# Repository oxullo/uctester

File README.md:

# uctester

Ultimate Continuity tester or Leo's ideal tool for continuity testing.

The design of the tool is described here: https://www.youtube.com/watch?v=N2M-p-OGvPg

A description of an implementation of such design can be found here: https://www.xul.it/blog/index.php/2020/08/15/the-ultimate-continuity-tester/

## Eagle

This repo stores the production files of the tool, with sources for Eagle and a Gerber export. All the files are released under the MIT license, with the permission of the original author.

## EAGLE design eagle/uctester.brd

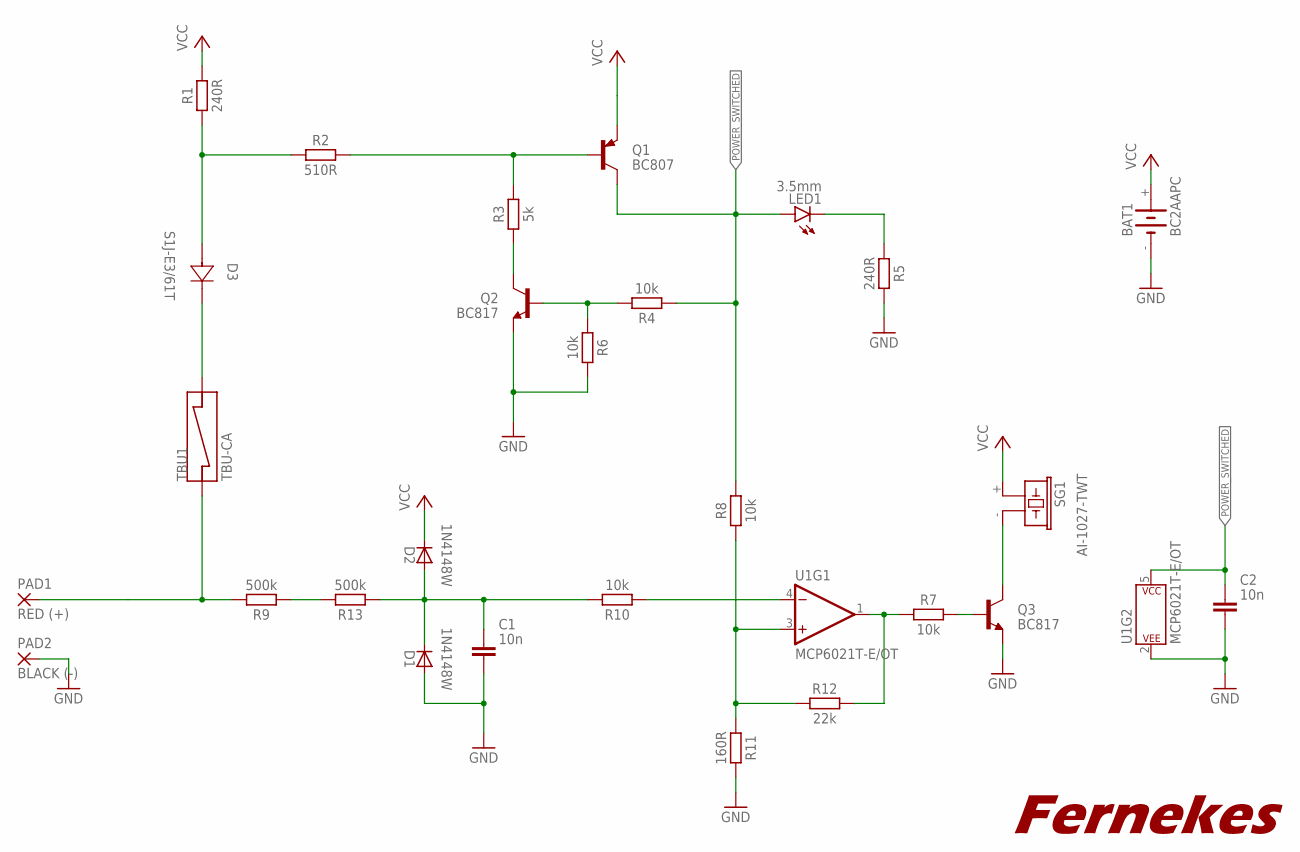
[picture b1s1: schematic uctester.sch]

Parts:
BAT1: BC2AAPC
C1, C2: 10n; CAPC3216X135
D1, D2: 1N4148W; SOD-123
D3: S1J-E3/61T; DIODE_DO214AC
LED1: 3.5mm; LED5MM
PAD1: RED (+); SMD2,54-5,08
PAD2: BLACK (-); SMD2,54-5,08
Q1: BC807; SOT23-BEC
Q2, Q3: BC817; SOT23-BEC
R1, R5: 240R; RESC3216X70
R2: 510R; RESC3216X70
R3: 5k; RESC3216X70
R4, R6, R7, R8, R10: 10k; RESC3216X70
R9, R13: 500k; RESC3216X70
R11: 160R; RESC3216X70
R12: 22k; RESC3216X70
SG1: AI-1027-TWT
TBU1: TBU-CA; RESDFN650X400X90-2N
U1: MCP6021T-E/OT; SOT95P280X145-5N

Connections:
GND: BAT1.-, C1.2, C2.2, D1.A, PAD2.1, Q2.E, Q3.E, R5.2, R6.2, R11.2, U1.2 (P$V-)
unnamed: Q2.C, R3.1
unnamed: Q2.B, R4.2, R6.1
unnamed: R9.1, R13.2
unnamed: R10.1, U1.4 (-IN)
unnamed: R8.1, R11.1, R12.1, U1.3 (+IN)
unnamed: R7.1, R12.2, U1.1 (OUT)
unnamed: Q3.B, R7.2
unnamed: Q3.C, SG1.- (2)
unnamed: Q1.B, R2.2, R3.2
unnamed: C1.1, D1.C, D2.A, R10.2, R13.1
unnamed: D3.2 (A), R1.1, R2.1
unnamed: PAD1.1, R9.2, TBU1.1
unnamed: LED1.K (C), R5.1
unnamed: D3.1 (C), TBU1.3
POWER_SWITCHED: C2.1, LED1.A, Q1.C, R4.1, R8.2, U1.5 (P$V+)
VCC: BAT1.+, D2.C, Q1.E, R1.2, SG1.+ (1)

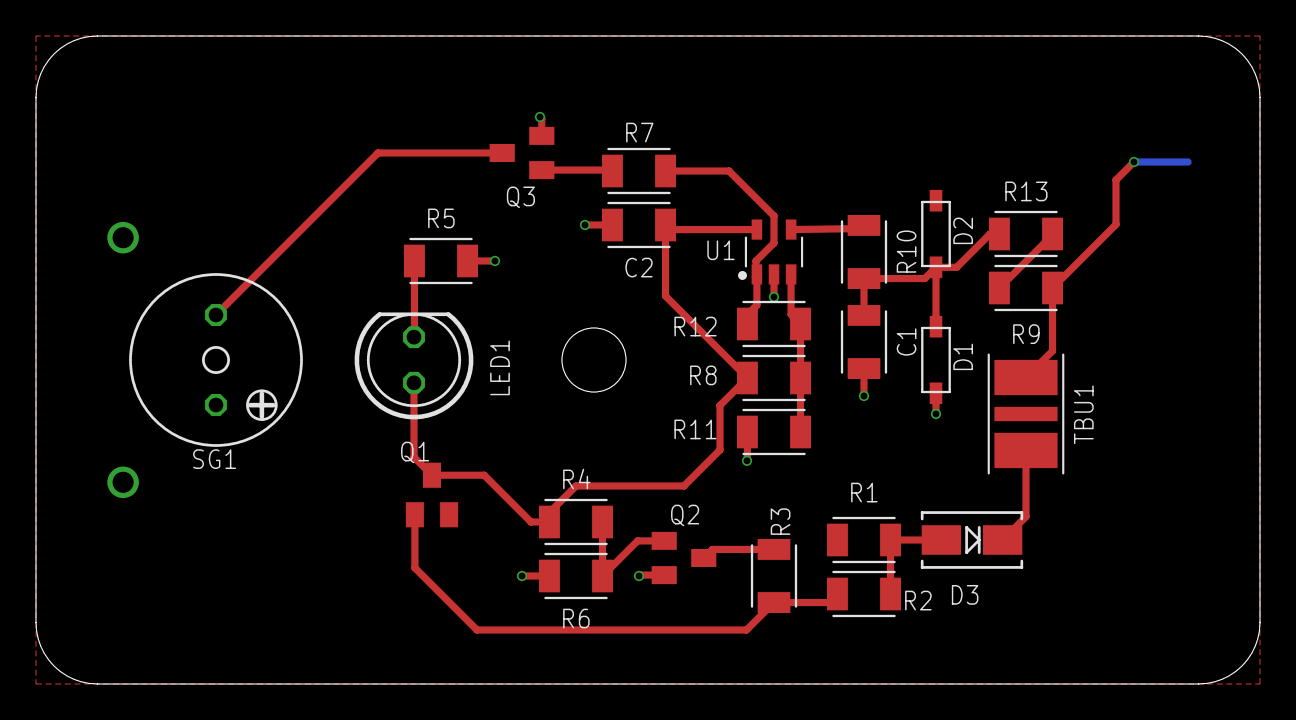
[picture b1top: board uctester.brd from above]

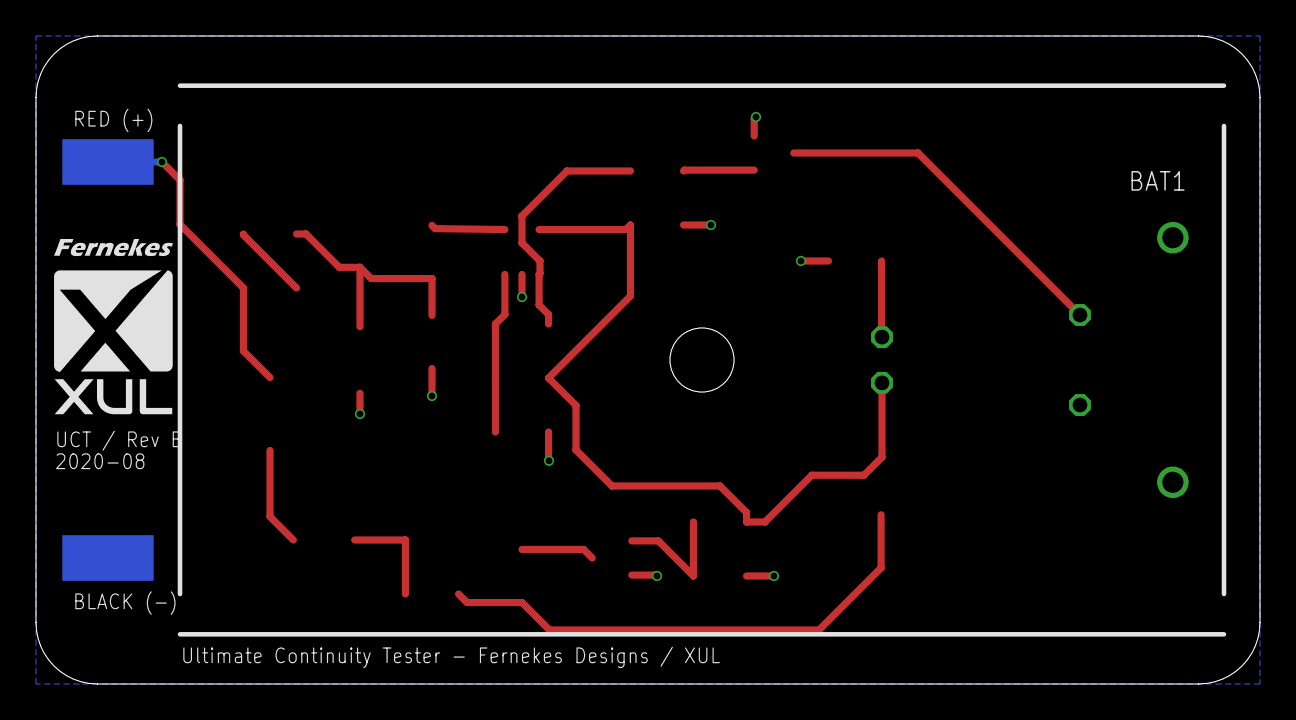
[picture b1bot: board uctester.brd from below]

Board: 2 copper layers, 68.0 x 36.0 mm, 29 parts (4 on the bottom side), 17 nets.

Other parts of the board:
U$1: XUL-LOGO-8MMH

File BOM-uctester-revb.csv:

Qty,Value,Device,Package,Parts,Description,Digikey
1,,LED5MM,LED5MM,LED1,LED,67-1097-ND
2,10n,C_CHIP-1206(3216-METRIC),CAPC3216X135,"C1, C2",Capacitor - Generic,478-1542-1-ND
5,10k,R_CHIP-1206(3216-METRIC),RESC3216X70,"R4, R6, R7, R8, R10",Resistor Fixed - Generic,311-10.0KFRCT-ND
1,160R,R_CHIP-1206(3216-METRIC),RESC3216X70,R11,Resistor Fixed - Generic,311-160FRCT-ND
1,22k,R_CHIP-1206(3216-METRIC),RESC3216X70,R12,Resistor Fixed - Generic,311-22.0KFRCT-ND
2,240R,R_CHIP-1206(3216-METRIC),RESC3216X70,"R1, R5",Resistor Fixed - Generic,311-240FRCT-ND
2,510k,R_CHIP-1206(3216-METRIC),RESC3216X70,"R9, R13",Resistor Fixed - Generic,311-510KFRCT-ND
1,510R,R_CHIP-1206(3216-METRIC),RESC3216X70,R2,Resistor Fixed - Generic,RMCF1206FT510RCT-ND
1,5k,R_CHIP-1206(3216-METRIC),RESC3216X70,R3,Resistor Fixed - Generic,YAG5090CT-ND
1,AI-1027-TWT,AI-1027-TWT,AI-1027-TWT,SG1,BUZZER Source: Buerklin,668-1219-ND
2,1N4148W,DIODESOD-123,SOD-123,"D1, D2",Diode,1N4148W-13FDICT-ND
1,BC2AAPC,BC2AAPC,BC2AAPC,BAT1,BC2APPC,BC2AAPC-ND
1,BC807,BC807-40SMD,SOT23-BEC,Q1,PNP Transistror,1727-2917-1-ND
2,BC817,BC817-40LT1SMD,SOT23-BEC,"Q2, Q3",NPN Transistor,1727-2919-1-ND
1,MCP6021T-E/OT,MCP6021T-E/OT,SOT95P280X145-5N,U1,MCP6021T-E/OT OP AMP,MCP6021T-E/OTDKR-ND
1,S1J-E3/61T,S1J-E3/61T,DIODE_DO214AC,D3,,S1J-E3/61TGICT-ND
1,TBU-CA,TBU-CA,RESDFN650X400X90-2N,TBU1,,TBU-CA065-050-WHCT-ND
1,,Banana sockets,,,,501-2347-ND

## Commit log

2020-08-17 Initial import of the latest design
2020-08-17 Add readme and authors
2020-08-18 Fix R12's silkscreen name position
